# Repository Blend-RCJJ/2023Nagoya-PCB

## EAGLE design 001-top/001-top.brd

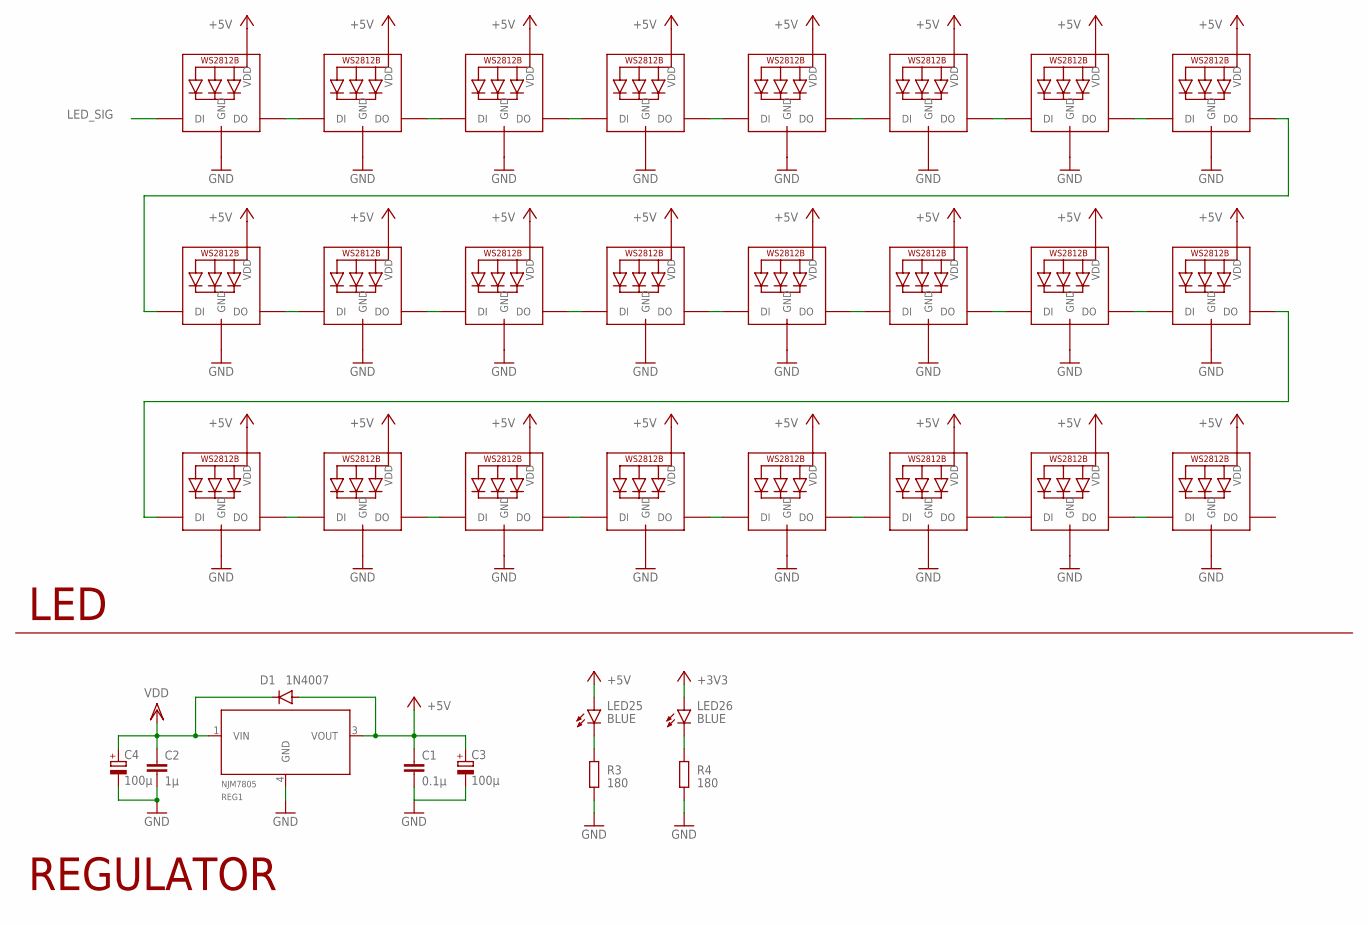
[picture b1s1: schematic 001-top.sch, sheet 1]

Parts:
C1: 0.1μ; C0402
C2: 1μ; C0402
C3, C4: 100μ; 153CLV-0505
D1: 1N4007; SMA-DO214AC
LED1, LED2, LED3, LED4, LED5, LED6, LED7, LED8, LED9, LED10, LED11, LED12, LED13, LED14, LED15, LED16, LED17, LED18, LED19, LED20, LED21, LED22, LED23, LED24: WS2812B_5050N; WS2812B-NARROW
LED25, LED26: BLUE; SML0603
R3, R4: 180; R0402
REG1: NJM7805; MYPARTS_D-PAK_TO252AA

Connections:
+3V3: LED26.A; also elsewhere on the board
+5V: C1.1, C3.+, D1.A, LED1.1-VDD (VDD), LED2.1-VDD (VDD), LED3.1-VDD (VDD), LED4.1-VDD (VDD), LED5.1-VDD (VDD), LED6.1-VDD (VDD), LED7.1-VDD (VDD), LED8.1-VDD (VDD), LED9.1-VDD (VDD), LED10.1-VDD (VDD), LED11.1-VDD (VDD), LED12.1-VDD (VDD), LED13.1-VDD (VDD), LED14.1-VDD (VDD), LED15.1-VDD (VDD), LED16.1-VDD (VDD), LED17.1-VDD (VDD), LED18.1-VDD (VDD), LED19.1-VDD (VDD), LED20.1-VDD (VDD), LED21.1-VDD (VDD), LED22.1-VDD (VDD), LED23.1-VDD (VDD), LED24.1-VDD (VDD), LED25.A, REG1.3 (VOUT); also elsewhere on the board
GND: C1.2, C2.2, C3.-, C4.-, LED1.3-GND (GND), LED2.3-GND (GND), LED3.3-GND (GND), LED4.3-GND (GND), LED5.3-GND (GND), LED6.3-GND (GND), LED7.3-GND (GND), LED8.3-GND (GND), LED9.3-GND (GND), LED10.3-GND (GND), LED11.3-GND (GND), LED12.3-GND (GND), LED13.3-GND (GND), LED14.3-GND (GND), LED15.3-GND (GND), LED16.3-GND (GND), LED17.3-GND (GND), LED18.3-GND (GND), LED19.3-GND (GND), LED20.3-GND (GND), LED21.3-GND (GND), LED22.3-GND (GND), LED23.3-GND (GND), LED24.3-GND (GND), R3.2, R4.2, REG1.4 (GND); also elsewhere on the board
LED_SIG: LED1.4-DIN (DI); also elsewhere on the board
LED_SIGNAL1: LED8.2-DOUT (DO), LED9.4-DIN (DI)
unnamed: LED1.2-DOUT (DO), LED2.4-DIN (DI)
unnamed: LED2.2-DOUT (DO), LED3.4-DIN (DI)
unnamed: LED3.2-DOUT (DO), LED4.4-DIN (DI)
unnamed: LED4.2-DOUT (DO), LED5.4-DIN (DI)
unnamed: LED5.2-DOUT (DO), LED6.4-DIN (DI)
unnamed: LED6.2-DOUT (DO), LED7.4-DIN (DI)
unnamed: LED7.2-DOUT (DO), LED8.4-DIN (DI)
unnamed: LED9.2-DOUT (DO), LED10.4-DIN (DI)
unnamed: LED10.2-DOUT (DO), LED11.4-DIN (DI)
unnamed: LED11.2-DOUT (DO), LED12.4-DIN (DI)
unnamed: LED12.2-DOUT (DO), LED13.4-DIN (DI)
unnamed: LED13.2-DOUT (DO), LED14.4-DIN (DI)
unnamed: LED14.2-DOUT (DO), LED15.4-DIN (DI)
unnamed: LED15.2-DOUT (DO), LED16.4-DIN (DI)
unnamed: LED17.2-DOUT (DO), LED18.4-DIN (DI)
unnamed: LED18.2-DOUT (DO), LED19.4-DIN (DI)
unnamed: LED19.2-DOUT (DO), LED20.4-DIN (DI)
unnamed: LED20.2-DOUT (DO), LED21.4-DIN (DI)
unnamed: LED21.2-DOUT (DO), LED22.4-DIN (DI)
unnamed: LED22.2-DOUT (DO), LED23.4-DIN (DI)
unnamed: LED23.2-DOUT (DO), LED24.4-DIN (DI)
unnamed: LED16.2-DOUT (DO), LED17.4-DIN (DI)
unnamed: LED25.C, R3.1
unnamed: LED26.C, R4.1
VDD: C2.1, C4.+, D1.K (C), REG1.1 (VIN); also elsewhere on the board

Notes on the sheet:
LED
REGULATOR

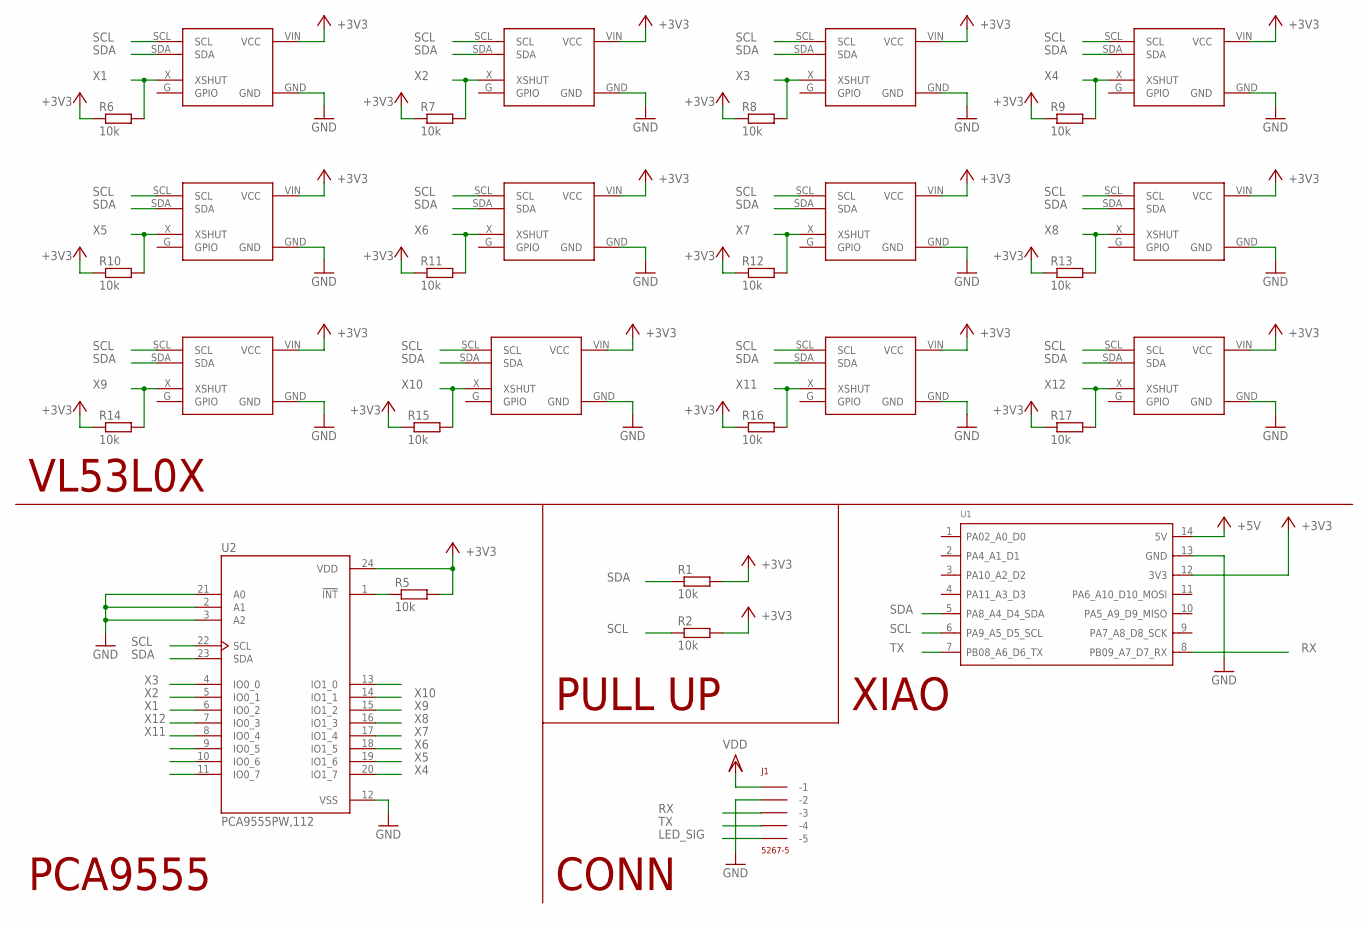
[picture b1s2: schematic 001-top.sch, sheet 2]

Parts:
J1: 5267-5
R1, R2, R5, R6, R7, R8, R9, R10, R11, R12, R13, R14, R15, R16, R17: 10k; R0402
U1: MOUDLE-SEEEDUINO-XIAO; MOUDLE14P-2.54-21X17.8MM
U2: PCA9555PW,112; SOP65P640X110-24N
VL1, VL2, VL3, VL4, VL5, VL6, VL7, VL8, VL9, VL10, VL11, VL12: VL53L0X; 1X04

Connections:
+3V3: R1.2, R2.2, R5.2, R6.1, R7.1, R8.1, R9.1, R10.1, R11.1, R12.1, R13.1, R14.1, R15.1, R16.1, R17.1, U1.12 (3V3), U2.24 (VDD), VL1.VIN (VCC), VL2.VIN (VCC), VL3.VIN (VCC), VL4.VIN (VCC), VL5.VIN (VCC), VL6.VIN (VCC), VL7.VIN (VCC), VL8.VIN (VCC), VL9.VIN (VCC), VL10.VIN (VCC), VL11.VIN (VCC), VL12.VIN (VCC); also elsewhere on the board
+5V: U1.14 (5V); also elsewhere on the board
GND: J1.P$2 (-2), U1.13 (GND), U2.2 (A1), U2.3 (A2), U2.12 (VSS), U2.21 (A0), VL1.GND, VL2.GND, VL3.GND, VL4.GND, VL5.GND, VL6.GND, VL7.GND, VL8.GND, VL9.GND, VL10.GND, VL11.GND, VL12.GND; also elsewhere on the board
LED_SIG: J1.P$5 (-5); also elsewhere on the board
unnamed: R5.1, U2.1 (!INT)
RX: J1.P$3 (-3), U1.8 (PB09_A7_D7_RX)
SCL: R2.1, U1.6 (PA9_A5_D5_SCL), U2.22 (SCL), VL1.SCL, VL2.SCL, VL3.SCL, VL4.SCL, VL5.SCL, VL6.SCL, VL7.SCL, VL8.SCL, VL9.SCL, VL10.SCL, VL11.SCL, VL12.SCL
SDA: R1.1, U1.5 (PA8_A4_D4_SDA), U2.23 (SDA), VL1.SDA, VL2.SDA, VL3.SDA, VL4.SDA, VL5.SDA, VL6.SDA, VL7.SDA, VL8.SDA, VL9.SDA, VL10.SDA, VL11.SDA, VL12.SDA
TX: J1.P$4 (-4), U1.7 (PB08_A6_D6_TX)
VDD: J1.P$1 (-1); also elsewhere on the board
X1: R6.2, U2.6 (IO0_2), VL1.X (XSHUT)
X2: R7.2, U2.5 (IO0_1), VL2.X (XSHUT)
X3: R8.2, U2.4 (IO0_0), VL3.X (XSHUT)
X4: R9.2, U2.20 (IO1_7), VL4.X (XSHUT)
X4\: U2.13 (IO1_0)
X5: R10.2, U2.19 (IO1_6), VL5.X (XSHUT)
X6: R11.2, U2.18 (IO1_5), VL6.X (XSHUT)
X7: R12.2, U2.17 (IO1_4), VL7.X (XSHUT)
X8: R13.2, U2.16 (IO1_3), VL8.X (XSHUT)
X9: R14.2, U2.15 (IO1_2), VL9.X (XSHUT)
X10: R15.2, U2.14 (IO1_1), VL10.X (XSHUT)
X11: R16.2, U2.8 (IO0_4), VL11.X (XSHUT)
X12: R17.2, U2.7 (IO0_3), VL12.X (XSHUT)

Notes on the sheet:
VL53L0X
PCA9555
PULL UP
CONN
XIAO

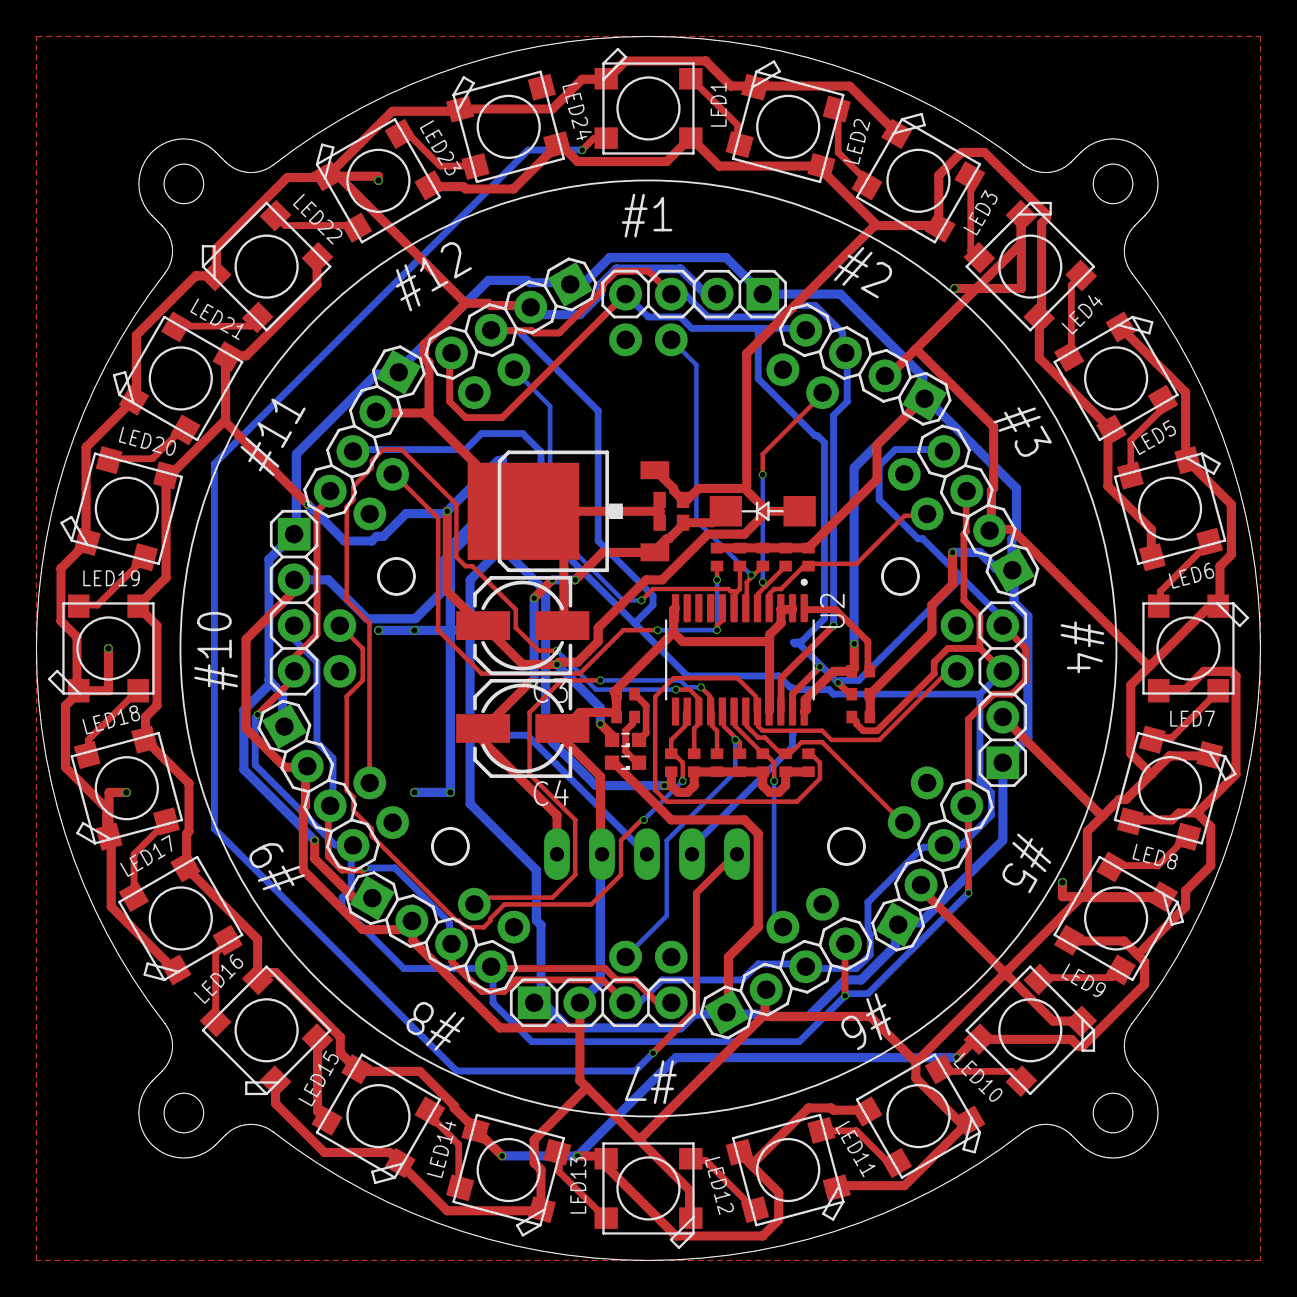
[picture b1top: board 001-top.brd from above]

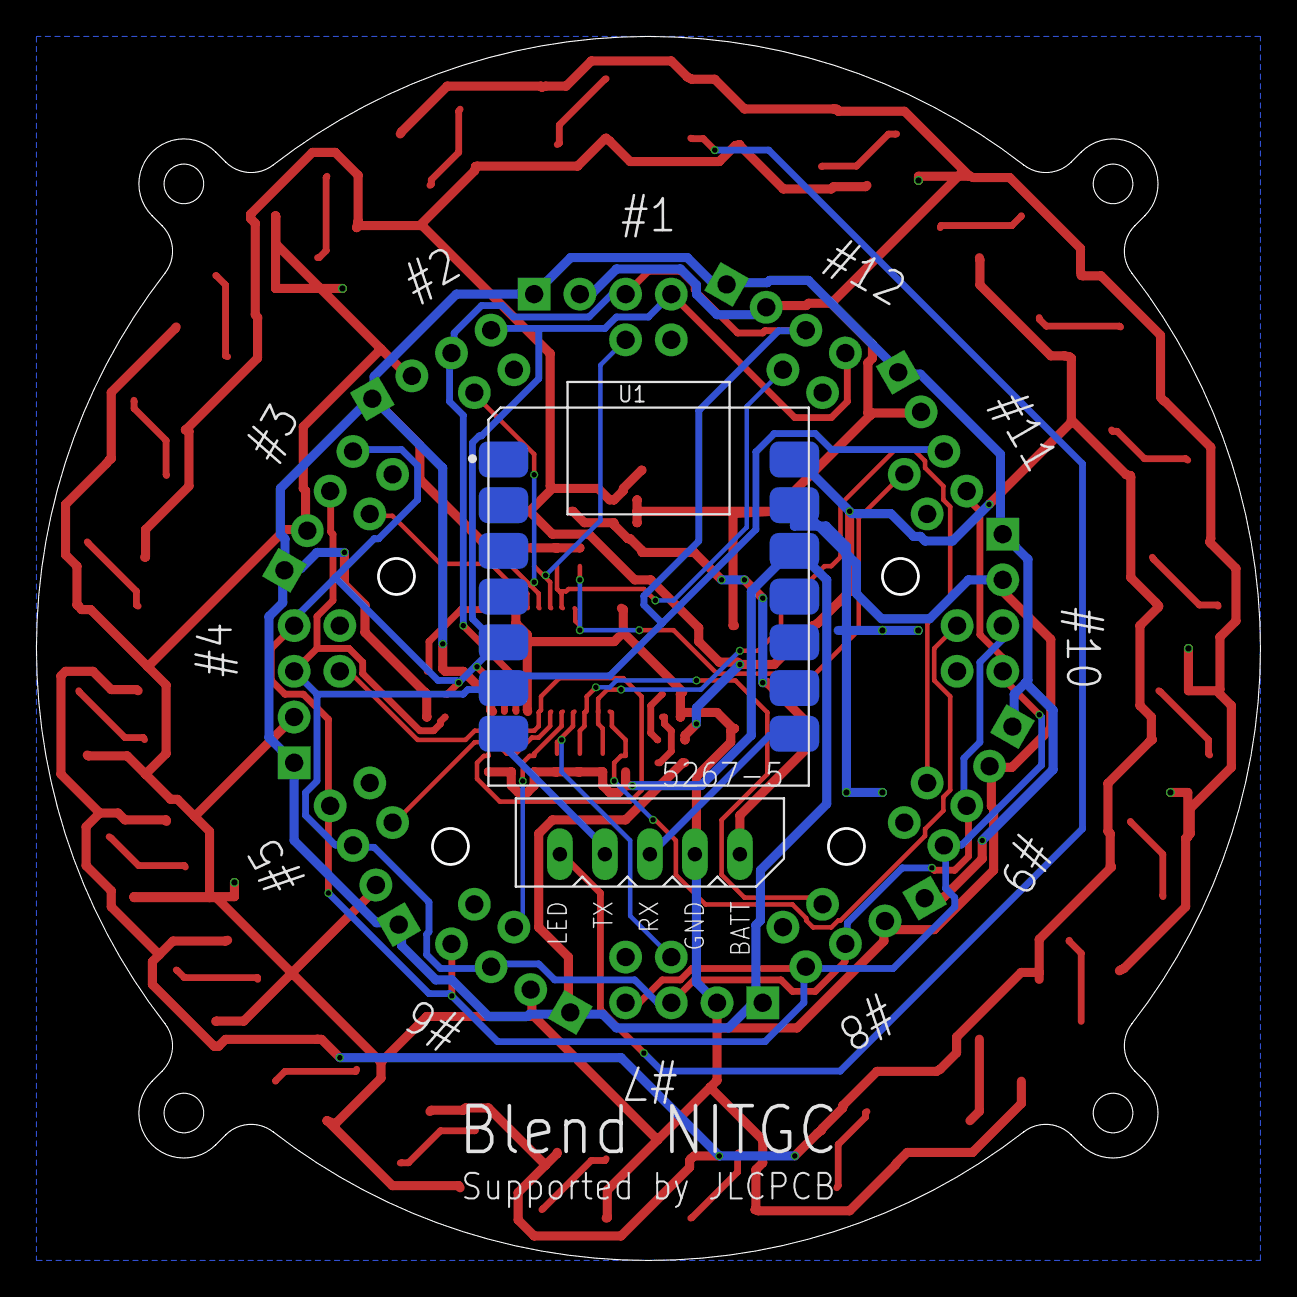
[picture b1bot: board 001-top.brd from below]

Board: 2 copper layers, 68.0 x 68.0 mm, 64 parts (2 on the bottom side), 47 nets.

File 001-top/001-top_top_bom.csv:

Comment,Designator,Footprint,LCSC Part #
0.1μ,C1,C0402,C141382
1N4007,D1,SMA-DO214AC,C727081
1μ,C2,C0402,C52923
10k,R1 R2 R5 R6 R7 R8 R9 R10 R11 R12 R13 R14 R15 R16 R17,R0402,C269674
100μ,C3 C4,153CLV-0505,C96178
180,R3 R4,R0402,C38941
BLUE,LED25 LED26,SML0603,C118339
NJM7805,REG1,MYPARTS_D-PAK_TO252AA,
PCA9555PW 112,U2,SOP65P640X110-24N,C128392
WS2812B_5050N,LED1 LED2 LED3 LED4 LED5 LED6 LED7 LED8 LED9 LED10 LED11 LED12 LED13 LED14 LED15 LED16 LED17 LED18 LED19 LED20 LED21 LED22 LED23 LED24,WS2812B-NARROW,C2874885

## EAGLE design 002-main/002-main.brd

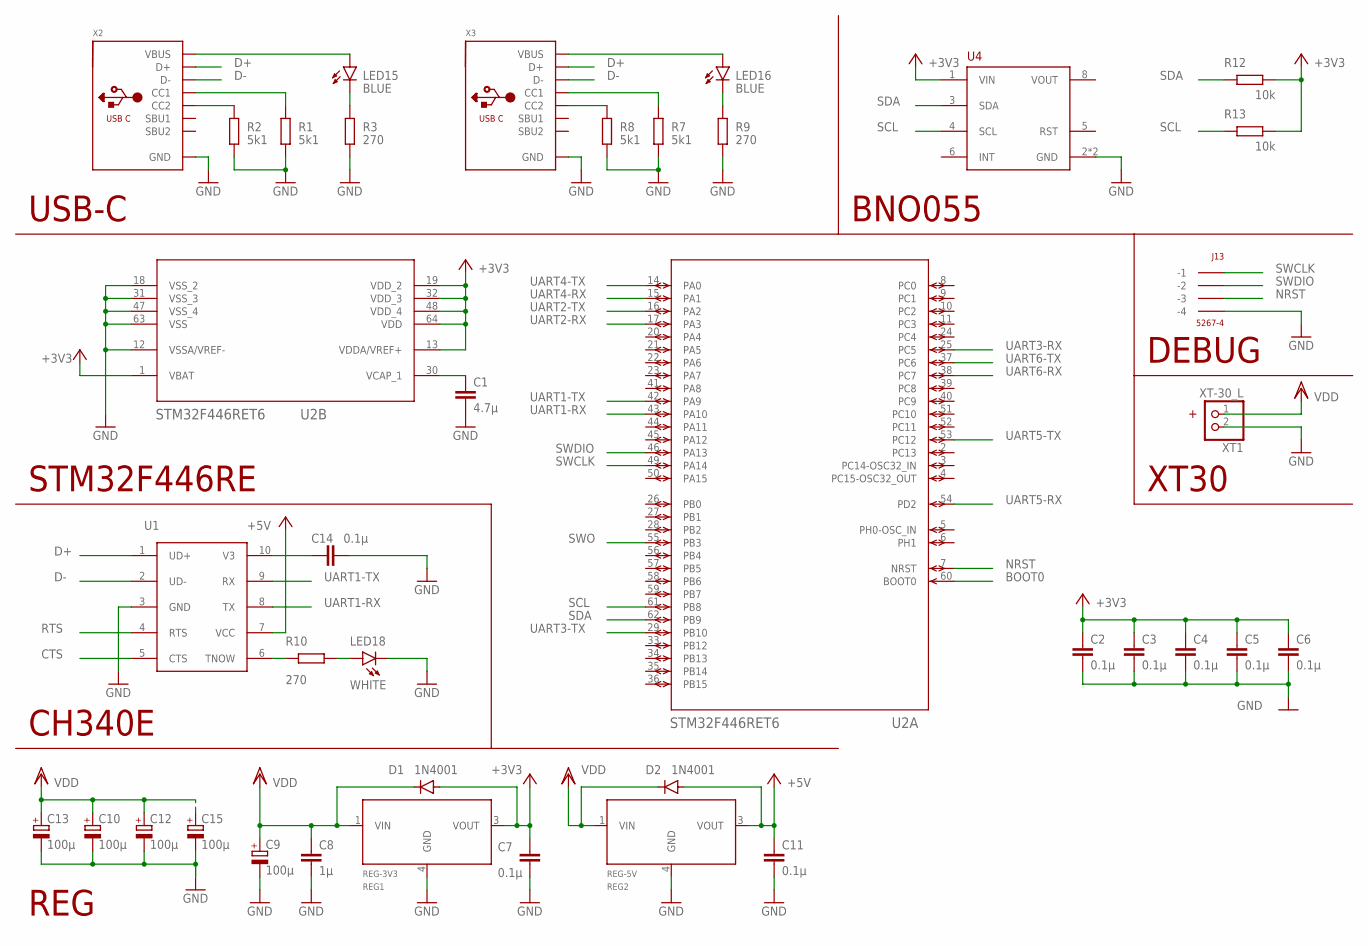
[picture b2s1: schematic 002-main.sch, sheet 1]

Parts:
C1: 4.7µ; C0603
C2, C3, C4, C5, C6, C7, C11, C14: 0.1µ; C0603
C8: 1µ; C0603
C9, C10, C12, C13, C15: 100μ; 153CLV-0505
D1, D2: 1N4001; SMA-DO214AC
J13: 5267-4
LED15, LED16: BLUE; SML0603
LED18: WHITE; SML0603
R1, R2, R7, R8: 5k1; R0402
R3, R9, R10: 270; R0402
R12, R13: 10k; R0402
REG1: REG-3V3; MYPARTS_D-PAK_TO252AA
REG2: REG-5V; MYPARTS_D-PAK_TO252AA
U1: CH340ESMD; MSOP10
U2: STM32F446RET6; LQFP64-10X10MM
U4: BNO055; SOCKET-08
X2, X3: USB_C; USB_C_CUSB31-CFM2AX-01-X
XT1: XT-30_L

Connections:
+3V3: C2.1, C3.1, C4.1, C5.1, C6.1, C7.1, D1.A, R12.1, R13.1, REG1.3 (VOUT), U2.1 (VBAT), U2.13 (VDDA/VREF+), U2.19 (VDD_2), U2.32 (VDD_3), U2.48 (VDD_4), U2.64 (VDD), U4.1 (VIN); also elsewhere on the board
+5V: C11.1, D2.A, REG2.3 (VOUT), U1.7 (VCC); also elsewhere on the board
BOOT0: U2.60 (BOOT0); also elsewhere on the board
CTS: U1.5 (CTS)
D+: U1.1 (UD+), X2.A6 (D+), X2.B6 (D+), X3.A6 (D+), X3.B6 (D+)
D-: U1.2 (UD-), X2.A7 (D-), X2.B7 (D-), X3.A7 (D-), X3.B7 (D-)
GND: C1.2, C2.2, C3.2, C4.2, C5.2, C6.2, C7.2, C8.2, C9.-, C10.-, C11.2, C12.-, C13.-, C14.2, C15.-, J13.P$4 (-4), LED18.C, R1.2, R2.2, R3.1, R7.2, R8.2, R9.1, REG1.4 (GND), REG2.4 (GND), U1.3 (GND), U2.12 (VSSA/VREF-), U2.18 (VSS_2), U2.31 (VSS_3), U2.47 (VSS_4), U2.63 (VSS), U4.2 (GND), U4.7 (GND), X2.A1B12 (GND), X2.B1A12 (GND), X3.A1B12 (GND), X3.B1A12 (GND), XT1.2; also elsewhere on the board
unnamed: C14.1, U1.10 (V3)
unnamed: R1.1, X2.A5 (CC1)
unnamed: R2.1, X2.B5 (CC2)
unnamed: LED15.C, R3.2
unnamed: C1.1, U2.30 (VCAP_1)
unnamed: R10.2, U1.6 (TNOW)
unnamed: LED18.A, R10.1
unnamed: R7.1, X3.A5 (CC1)
unnamed: R8.1, X3.B5 (CC2)
unnamed: LED15.A, X2.A4B9 (VBUS), X2.B4A9 (VBUS)
unnamed: LED16.A, X3.A4B9 (VBUS), X3.B4A9 (VBUS)
unnamed: LED16.C, R9.2
NRST: J13.P$3 (-3), U2.7 (NRST); also elsewhere on the board
RTS: U1.4 (RTS)
SCL: R13.2, U2.61 (PB8), U4.4 (SCL)
SDA: R12.2, U2.62 (PB9), U4.3 (SDA)
SWCLK: J13.P$1 (-1), U2.49 (PA14)
SWDIO: J13.P$2 (-2), U2.46 (PA13)
SWO: U2.55 (PB3)
UART1-RX: U1.8 (TX), U2.43 (PA10)
UART1-TX: U1.9 (RX), U2.42 (PA9)
UART2-RX: U2.17 (PA3); also elsewhere on the board
UART2-TX: U2.16 (PA2); also elsewhere on the board
UART3-RX: U2.25 (PC5); also elsewhere on the board
UART3-TX: U2.29 (PB10); also elsewhere on the board
UART4-RX: U2.15 (PA1); also elsewhere on the board
UART4-TX: U2.14 (PA0); also elsewhere on the board
UART5-RX: U2.54 (PD2); also elsewhere on the board
UART5-TX: U2.53 (PC12); also elsewhere on the board
UART6-RX: U2.38 (PC7); also elsewhere on the board
UART6-TX: U2.37 (PC6); also elsewhere on the board
VDD: C8.1, C9.+, C10.+, C12.+, C13.+, C15.+, D1.K (C), D2.K (C), REG1.1 (VIN), REG2.1 (VIN), XT1.1; also elsewhere on the board
VOUT: U4.8 (VOUT)

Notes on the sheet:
STM32F446RE
REG
CH340E
USB-C
DEBUG
XT30
BNO055

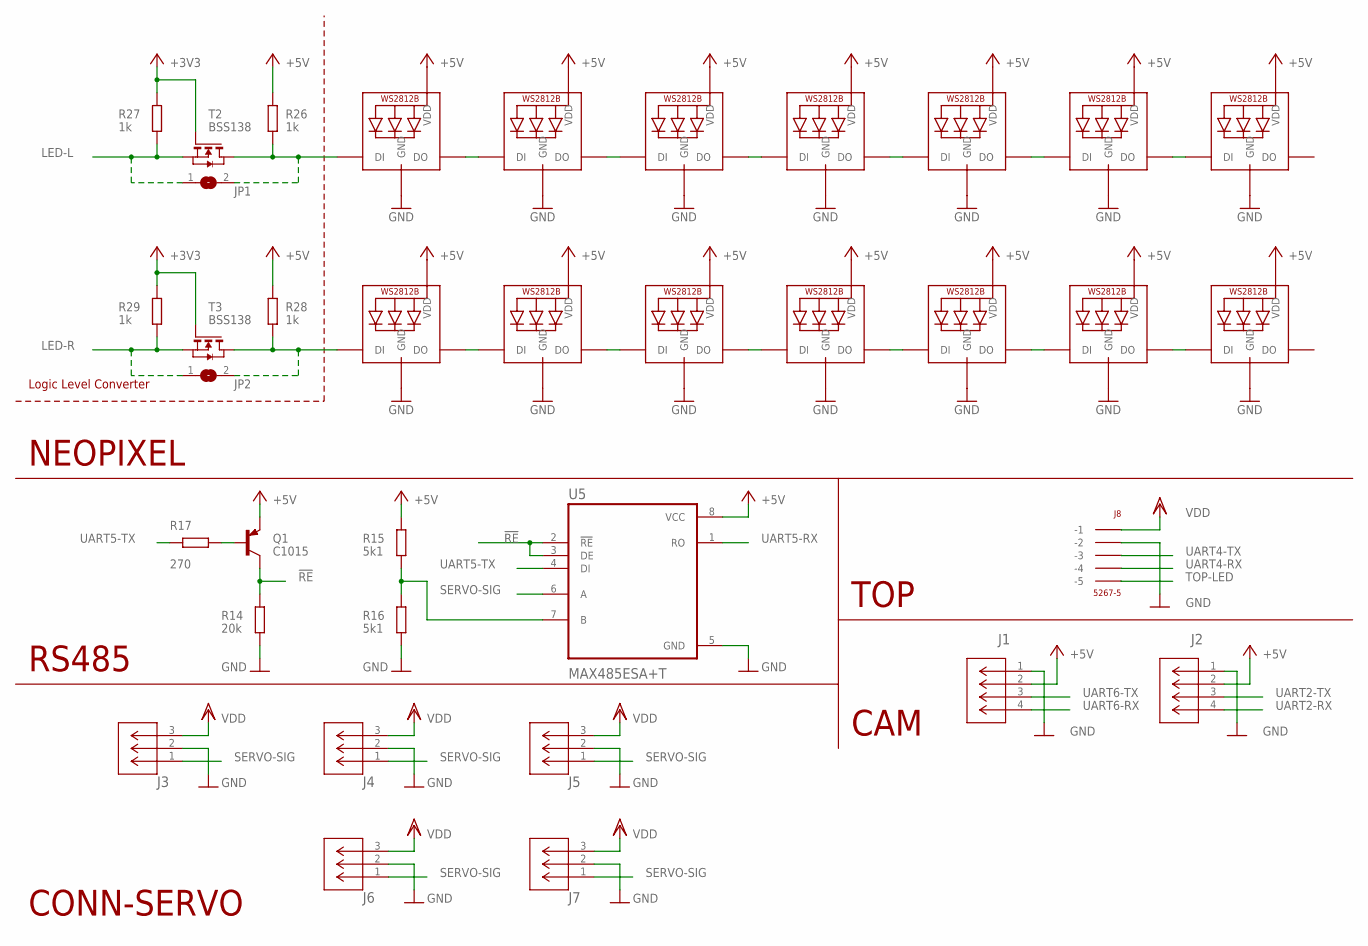
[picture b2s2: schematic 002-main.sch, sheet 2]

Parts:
J1, J2: 22057045; CON_22057045_MOL
J3, J4, J5, J6, J7: 22057035; CON_22057035_MOL
J8: 5267-5
JP1, JP2: JP2
LED1, LED2, LED3, LED4, LED5, LED6, LED7, LED8, LED9, LED10, LED11, LED12, LED13, LED14: WS2812B_2020
Q1: C1015; SOT23
R14: 20k; R0402
R15, R16: 5k1; R0402
R17: 270; R0402
R26, R27, R28, R29: 1k; R0402
T2, T3: BSS138; SOT-23
U5: MAX485ESA+T; SOIC127P600X175-8N

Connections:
!RE: Q1.3 (C), R14.1, U5.2 (!RE), U5.3 (DE)
+3V3: R27.1, R29.1, T2.3 (G), T3.3 (G); also elsewhere on the board
+5V: J1.2, J2.2, LED1.4 (VDD), LED2.4 (VDD), LED3.4 (VDD), LED4.4 (VDD), LED5.4 (VDD), LED6.4 (VDD), LED7.4 (VDD), LED8.4 (VDD), LED9.4 (VDD), LED10.4 (VDD), LED11.4 (VDD), LED12.4 (VDD), LED13.4 (VDD), LED14.4 (VDD), Q1.2 (E), R15.1, R26.1, R28.1, U5.8 (VCC); also elsewhere on the board
GND: J1.1, J2.1, J3.2, J4.2, J5.2, J6.2, J7.2, J8.P$2 (-2), LED1.2 (GND), LED2.2 (GND), LED3.2 (GND), LED4.2 (GND), LED5.2 (GND), LED6.2 (GND), LED7.2 (GND), LED8.2 (GND), LED9.2 (GND), LED10.2 (GND), LED11.2 (GND), LED12.2 (GND), LED13.2 (GND), LED14.2 (GND), R14.2, R16.2, U5.5 (GND); also elsewhere on the board
LED-L: JP1.1, R27.2, T2.2 (S)
LED-L-5V: JP1.2, LED1.3 (DI), R26.2, T2.1 (D)
LED-R: JP2.1, R29.2, T3.2 (S)
LED-R-5V: JP2.2, LED8.3 (DI), R28.2, T3.1 (D)
unnamed: LED1.1 (DO), LED2.3 (DI)
unnamed: LED2.1 (DO), LED3.3 (DI)
unnamed: LED3.1 (DO), LED4.3 (DI)
unnamed: LED4.1 (DO), LED5.3 (DI)
unnamed: LED5.1 (DO), LED6.3 (DI)
unnamed: LED6.1 (DO), LED7.3 (DI)
unnamed: LED8.1 (DO), LED9.3 (DI)
unnamed: LED9.1 (DO), LED10.3 (DI)
unnamed: LED10.1 (DO), LED11.3 (DI)
unnamed: LED11.1 (DO), LED12.3 (DI)
unnamed: LED12.1 (DO), LED13.3 (DI)
unnamed: LED13.1 (DO), LED14.3 (DI)
unnamed: Q1.1 (B), R17.1
unnamed: R15.2, R16.1, U5.7 (B)
SERVO-SIG: J3.1, J4.1, J5.1, J6.1, J7.1, U5.6 (A)
TOP-LED: J8.P$5 (-5)
UART2-RX: J2.4; also elsewhere on the board
UART2-TX: J2.3; also elsewhere on the board
UART4-RX: J8.P$4 (-4); also elsewhere on the board
UART4-TX: J8.P$3 (-3); also elsewhere on the board
UART5-RX: U5.1 (RO); also elsewhere on the board
UART5-TX: R17.2, U5.4 (DI); also elsewhere on the board
UART6-RX: J1.4; also elsewhere on the board
UART6-TX: J1.3; also elsewhere on the board
VDD: J3.3, J4.3, J5.3, J6.3, J7.3, J8.P$1 (-1); also elsewhere on the board

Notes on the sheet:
NEOPIXEL
TOP
CONN-SERVO
CAM
RS485
Logic Level Converter

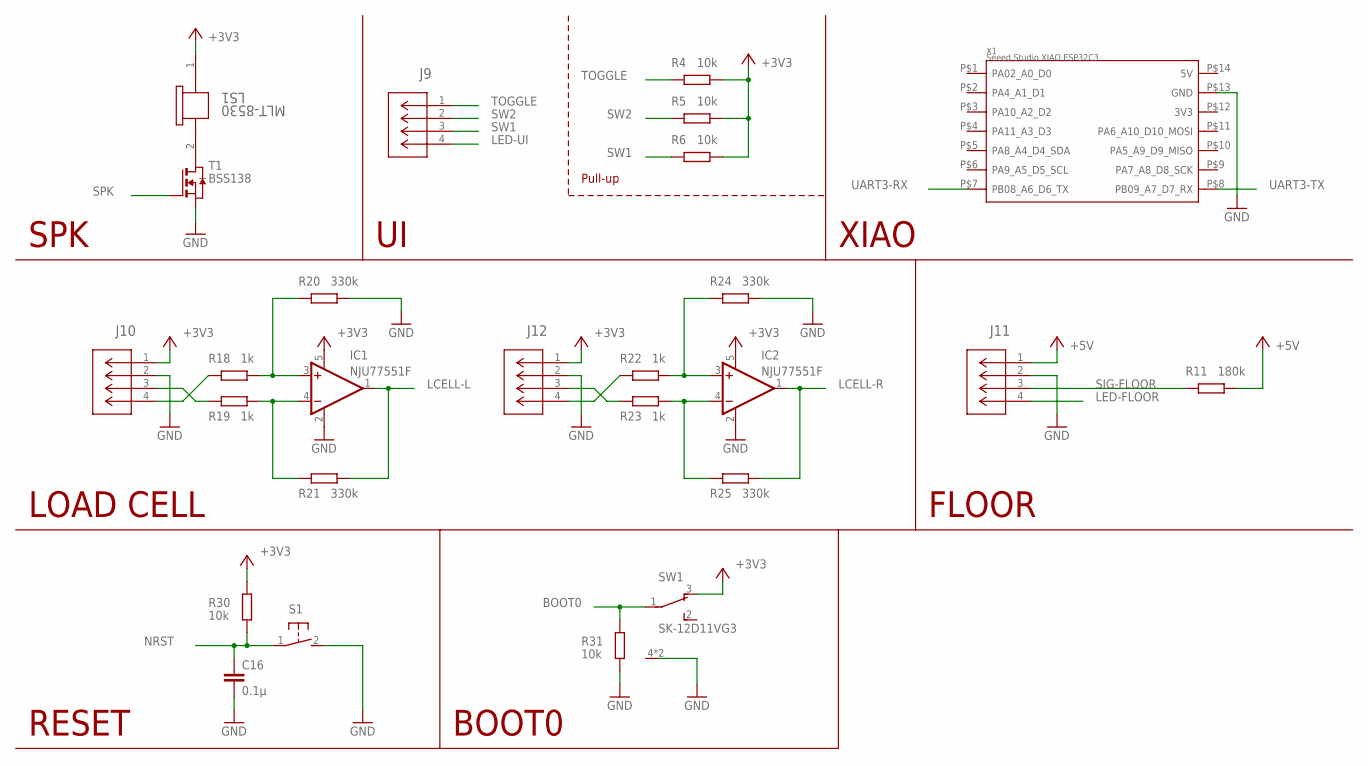
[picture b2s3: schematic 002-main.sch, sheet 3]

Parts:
C16: 0.1µ; C0603
IC1, IC2: NJU77551F; SOT23-5
J9, J10, J11, J12: 22057045; CON_22057045_MOL
LS1: MLT-8530; MLT-8530_JHE
R4, R5, R6, R30, R31: 10k; R0402
R11: 180k; R0402
R18, R19, R22, R23: 1k; R0402
R20, R21, R24, R25: 330k; R0402
S1: 31-XX; B3F-31XX
SW1: SK-12D11VG3
T1: BSS138; SOT-23
X1: Seeed Studio XIAO ESP32C3; XIAO-PINHEAD

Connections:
+3V3: IC1.5 (V+), IC2.5 (V+), J10.1, J12.1, LS1.1, R4.1, R5.1, R6.1, R30.1, SW1.3 (O); also elsewhere on the board
+5V: J11.1, R11.1; also elsewhere on the board
BOOT0: R31.1, SW1.1; also elsewhere on the board
GND: C16.2, IC1.2 (V-), IC2.2 (V-), J10.2, J11.2, J12.2, R20.1, R24.1, R31.2, S1.2 (S), SW1.4 (CASE), SW1.5 (CASE), T1.2 (S), X1.P$13 (GND); also elsewhere on the board
LCELL-L: IC1.1 (OUT), R21.1
LCELL-R: IC2.1 (OUT), R25.1
LED-FLOOR: J11.4
LED-UI: J9.4
unnamed: LS1.2, T1.1 (D)
unnamed: IC1.3 (+IN), R18.1, R20.2
unnamed: IC1.4 (-IN), R19.1, R21.2
unnamed: J10.3, R19.2
unnamed: J10.4, R18.2
unnamed: IC2.3 (+IN), R22.1, R24.2
unnamed: IC2.4 (-IN), R23.1, R25.2
unnamed: J12.4, R22.2
unnamed: J12.3, R23.2
NRST: C16.1, R30.2, S1.1; also elsewhere on the board
SIG-FLOOR: J11.3, R11.2
SPK: T1.3 (G)
SW1: J9.3, R6.2
SW2: J9.2, R5.2
TOGGLE: J9.1, R4.2
UART3-RX: X1.P$7 (PB08_A6_D6_TX); also elsewhere on the board
UART3-TX: X1.P$8 (PB09_A7_D7_RX); also elsewhere on the board

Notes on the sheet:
XIAO
SPK
Pull-up
FLOOR
LOAD CELL
RESET
BOOT0

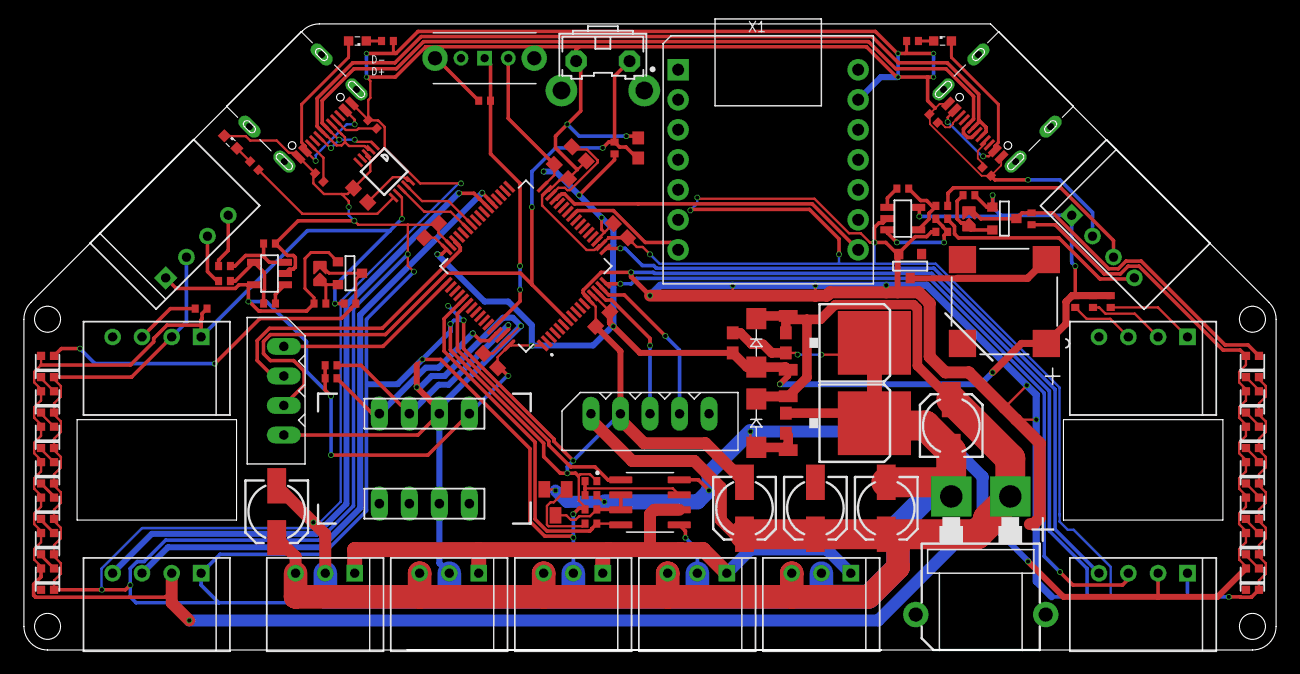
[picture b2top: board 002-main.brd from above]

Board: 2 copper layers, 106.0 x 53.0 mm, 100 parts (0 on the bottom side), 71 nets.

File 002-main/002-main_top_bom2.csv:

Comment,Designator,Footprint,LCSC Part #
0.1µ,C2 C3 C4 C5 C6 C7 C11 C14 C16,C0603,C14663
1N4001,D1 D2 D3,SMA-DO214AC,C727079
1k,R18 R19 R22 R23 R26 R27 R28 R29,R0402,C11702
1µ,C8,C0603,C15849
4.7µ,C1,C0603,C19666
5k1,R1 R2 R7 R8,R0402,C25905
10k,R4 R5 R6 R12 R13 R30 R31,R0402,C25744
20k,R14,R0402,C25765
100μ,C9 C10 C12 C13 C15,153CLV-0505,C72487
180k,R11,R0402,C25760
270,R3 R9 R10 R32,R0402,C25099
330k,R20 R21 R24 R25,R0402,C25778
BLUE,LED15 LED16,SML0603,C118339
BSS138,T1 T2 T3,SOT-23,C112239
C1015,Q1,SOT23,C181170
CH340ESMD,U1,MSOP10,C99652
MAX485ESA+T,U5,SOIC127P600X175-8N,MAX485ED
MLT-8530,LS1,MLT-8530_JHE,C94599
STM32F446RET6,U2,LQFP64-10X10MM,C69336
WHITE,LED17 LED18,SML0603,C189306
usb-c,X2 X3,USB_C_CUSB31-CFM2AX-01-X,C2987386
7k5,R17,R0402,C25918
2k2,R15 R16,R0402,C25879

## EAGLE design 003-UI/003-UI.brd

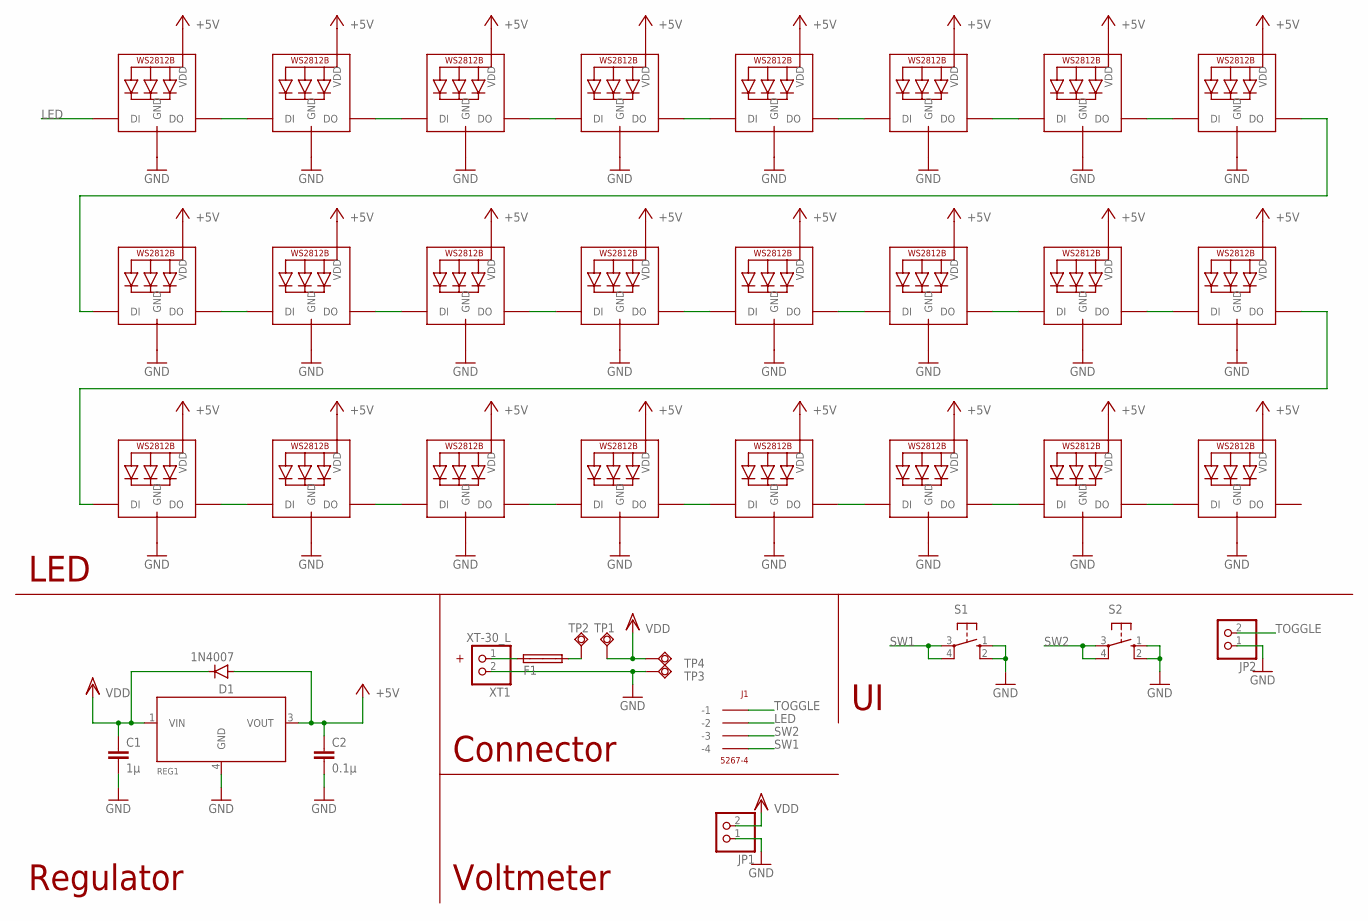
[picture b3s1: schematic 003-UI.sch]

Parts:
C1: 1μ; C0402
C2: 0.1µ; C0402
D1: 1N4007; SMA-DO214AC
F1: SHK20L
J1: 5267-4
JP1, JP2: PINHD-1X2; 1X02
LED1, LED2, LED3, LED4, LED5, LED6, LED7, LED8, LED9, LED10, LED11, LED12, LED13, LED14, LED15, LED16, LED17, LED18, LED19, LED20, LED21, LED22, LED23, LED24: WS2812B_2020
REG1: MYPARTS_NJM7800S-REGULATOR; MYPARTS_D-PAK_TO252AA
S1, S2: 10-XX; B3F-10XX
TP1, TP2, TP3, TP4: TPSQPAD1-20; P1-20
XT1: XT-30_L

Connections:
+5V: C2.1, D1.A, LED1.4 (VDD), LED2.4 (VDD), LED3.4 (VDD), LED4.4 (VDD), LED5.4 (VDD), LED6.4 (VDD), LED7.4 (VDD), LED8.4 (VDD), LED9.4 (VDD), LED10.4 (VDD), LED11.4 (VDD), LED12.4 (VDD), LED13.4 (VDD), LED14.4 (VDD), LED15.4 (VDD), LED16.4 (VDD), LED17.4 (VDD), LED18.4 (VDD), LED19.4 (VDD), LED20.4 (VDD), LED21.4 (VDD), LED22.4 (VDD), LED23.4 (VDD), LED24.4 (VDD), REG1.3 (VOUT)
GND: C1.2, C2.2, JP1.1, JP2.1, LED1.2 (GND), LED2.2 (GND), LED3.2 (GND), LED4.2 (GND), LED5.2 (GND), LED6.2 (GND), LED7.2 (GND), LED8.2 (GND), LED9.2 (GND), LED10.2 (GND), LED11.2 (GND), LED12.2 (GND), LED13.2 (GND), LED14.2 (GND), LED15.2 (GND), LED16.2 (GND), LED17.2 (GND), LED18.2 (GND), LED19.2 (GND), LED20.2 (GND), LED21.2 (GND), LED22.2 (GND), LED23.2 (GND), LED24.2 (GND), REG1.4 (GND), S1.1 (S), S1.2 (S1), S2.1 (S), S2.2 (S1), TP3.TP, XT1.2
LED: J1.P$2 (-2), LED1.3 (DI)
unnamed: LED2.1 (DO), LED3.3 (DI)
unnamed: F1.1A, XT1.1
unnamed: F1.2A, TP2.TP
unnamed: LED1.1 (DO), LED2.3 (DI)
unnamed: LED3.1 (DO), LED4.3 (DI)
unnamed: LED4.1 (DO), LED5.3 (DI)
unnamed: LED5.1 (DO), LED6.3 (DI)
unnamed: LED6.1 (DO), LED7.3 (DI)
unnamed: LED7.1 (DO), LED8.3 (DI)
unnamed: LED8.1 (DO), LED9.3 (DI)
unnamed: LED9.1 (DO), LED10.3 (DI)
unnamed: LED10.1 (DO), LED11.3 (DI)
unnamed: LED11.1 (DO), LED12.3 (DI)
unnamed: LED12.1 (DO), LED13.3 (DI)
unnamed: LED13.1 (DO), LED14.3 (DI)
unnamed: LED14.1 (DO), LED15.3 (DI)
unnamed: LED15.1 (DO), LED16.3 (DI)
unnamed: LED16.1 (DO), LED17.3 (DI)
unnamed: LED17.1 (DO), LED18.3 (DI)
unnamed: LED18.1 (DO), LED19.3 (DI)
unnamed: LED19.1 (DO), LED20.3 (DI)
unnamed: LED20.1 (DO), LED21.3 (DI)
unnamed: LED21.1 (DO), LED22.3 (DI)
unnamed: LED22.1 (DO), LED23.3 (DI)
unnamed: LED23.1 (DO), LED24.3 (DI)
SW1: J1.P$4 (-4), S1.3, S1.4 (P1)
SW2: J1.P$3 (-3), S2.3, S2.4 (P1)
TOGGLE: J1.P$1 (-1), JP2.2
VDD: C1.1, D1.K (C), JP1.2, REG1.1 (VIN), TP1.TP, TP4.TP

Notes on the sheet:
Regulator
Connector
Voltmeter
LED

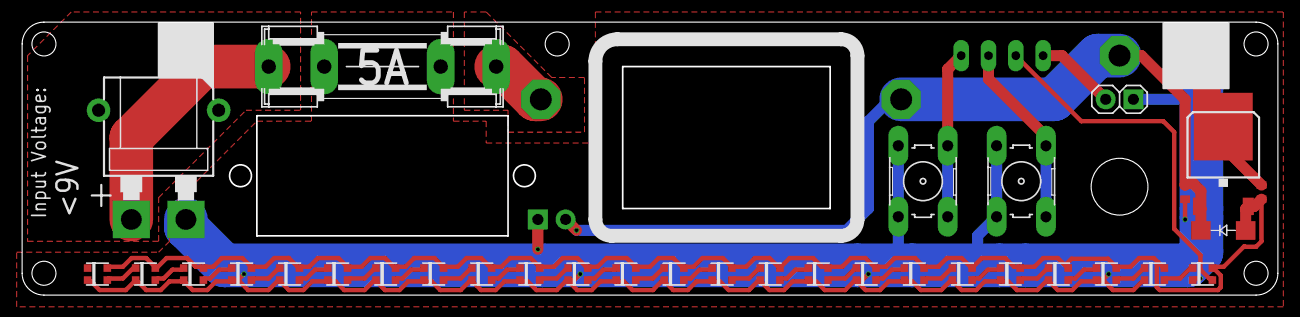
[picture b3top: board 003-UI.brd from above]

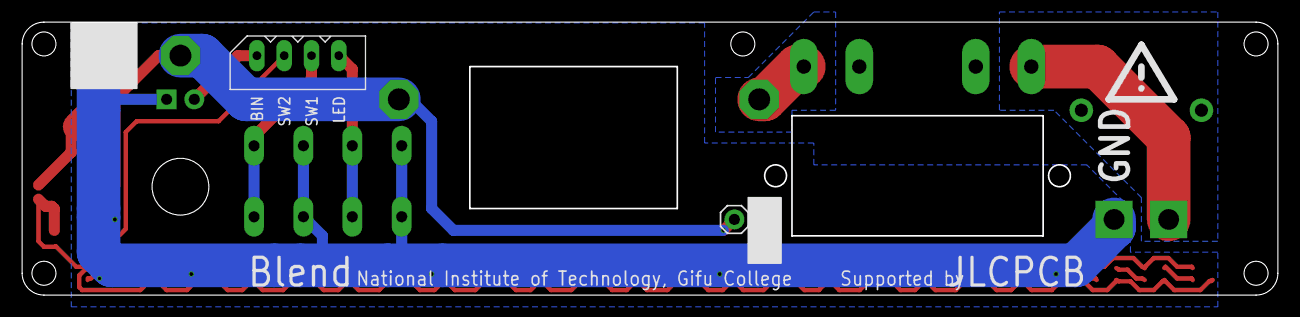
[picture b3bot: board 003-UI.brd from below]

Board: 2 copper layers, 115.0 x 25.0 mm, 39 parts (2 on the bottom side), 32 nets.

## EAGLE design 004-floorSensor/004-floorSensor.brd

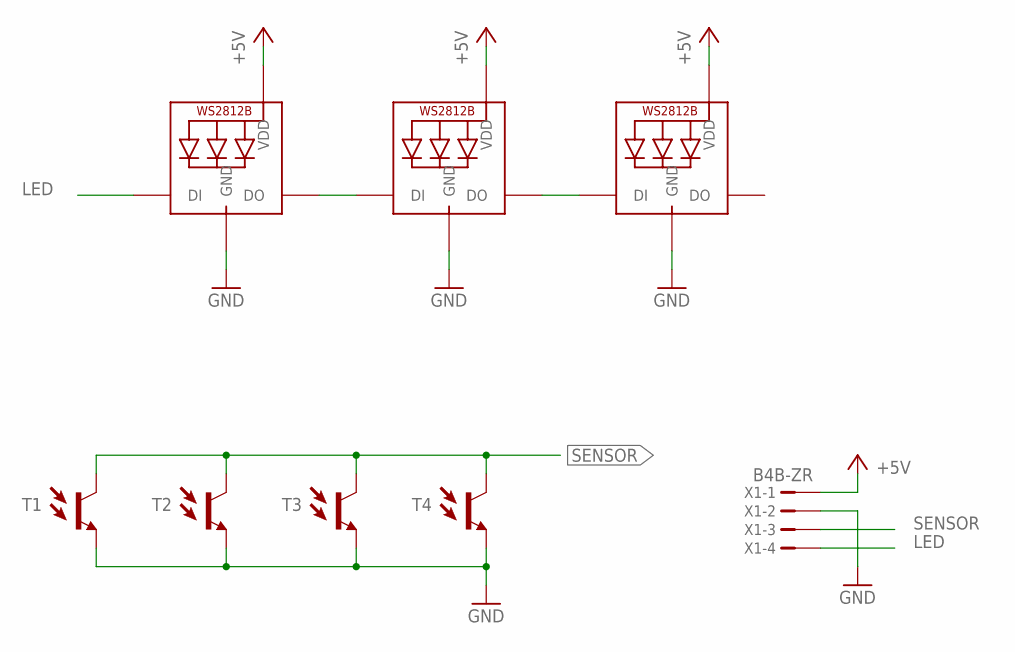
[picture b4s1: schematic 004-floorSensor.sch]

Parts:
LED1, LED2, LED3: WS2812B_5050N; WS2812B-NARROW
T1, T2, T3, T4: MYPARTS_NJL7502L
X1: B4B-ZR

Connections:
+5V: LED1.1-VDD (VDD), LED2.1-VDD (VDD), LED3.1-VDD (VDD), X1.1
GND: LED1.3-GND (GND), LED2.3-GND (GND), LED3.3-GND (GND), T1.E, T2.E, T3.E, T4.E, X1.2
LED: LED1.4-DIN (DI), X1.4
unnamed: LED1.2-DOUT (DO), LED2.4-DIN (DI)
unnamed: LED2.2-DOUT (DO), LED3.4-DIN (DI)
SENSOR: T1.C, T2.C, T3.C, T4.C, X1.3

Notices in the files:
parts and their libraries:
COPYRIGHT: Copyright (C) 2022 Ultra Librarian. All rights reserved.
